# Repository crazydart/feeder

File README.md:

# Feeder REV12CD

Public hardware fork maintained by **crazydart**, derived from [Opulo's feeder repository](https://github.com/opulo-inc/feeder). **REV12CD removes the alternate U2 MCU and keeps U1 (STM32F031C6T6, LQFP-48).** The single board and all three panel copies are labeled REV12CD.

| File | Purpose |
|---|---|
| [Single-board KiCad project](pcb/mobo/mobo.kicad_pro) | Editable circuit and PCB |
| [Three-board KiCad project](pcb/mobo-panel3/feeder-rev12cd-panel3.kicad_pro) | Editable routed panel |
| [JLCPCB upload ZIP](pcb/mobo-panel3/feeder-rev12cd-panel3-jlcpcb.zip) | PCB, drills and both stencil paste layers together |
| [PCB order notes](pcb/mobo-panel3/ORDER-NOTES.md) | Settings and short order comment |
| [Stencil and PnP data](pcb/mobo-panel3/STENCIL-AND-PNP.md) | Stencil settings and saved machine coordinates |
| [Panel documentation](pcb/mobo-panel3/README.md) | Reproduction steps and validation results |

The panel is 184 × 104 × 1.6 mm, with three boards and six drilled breakaway tabs per board. The top/bottom tabs and four side tabs avoid the connectors and buttons.

Modified 2026-10-11 from upstream commit `05843dd0e7551cbf20dc831514174f446f376858`. Checks found no new electrical DRC errors, unconnected items or single-board schematic/PCB mismatches. Inherited DRC/ERC findings are documented in the [single-board notes](pcb/mobo/README.md) and [panel validation reports](pcb/mobo-panel3/validation). This derivative has not been physically prototyped.

Hardware remains under CERN-OHL-W v2; see [LICENSE](LICENSE). The modified PCBs use AI Herding Cats branding and credit Opulo for the original design. Other upstream designs and documentation remain below.

## Accessories

- [Gridfinity holder for 8 mm feeders](cad/accessories/gridfinity-8mm-holder/README.md) — five slots on a 5 × 3 base, with STL and editable OpenSCAD source. Prototype 06 provides 10 mm of feeder lift and 4 mm radial rear relief for mounted reels; revised reel clearance awaits a physical fit check.
- [Gridfinity holder for 16 mm and 24 mm feeders](cad/accessories/gridfinity-2u-holder/README.md) — four slots on a 5 × 4 base, rendered with both 2u feeder models. Physical fit is untested.
- [Continuous 4 mm spool arm and threaded thimble](cad/accessories/threaded-thimble/README.md) — full arm thickness up to the cover-tape guard, with 12.4 mm of reel space and the tested retaining screw with its 30 × 3 mm head. Prototype 04 has no tapered neck; loaded stiffness awaits a print test.

## Parts sourcing

- [Feeder motor sourcing](docs/motor-sourcing.md) — motor specifications, supplier URLs, fit and wiring details, and the October 16, 2026 checkout costs for comparing direct imports with the Opulo kit.

## Upstream LumenPnP Feeders
The LumenPnP Feeders are open source pick and place feeders to aid in [Mid-Scale Manufacturing](https://stephenhawes.com/level-2-manufacturing/).

LumenPnP Feeders are available for sale on the [Opulo Website](https://www.opulo.io/). If you build or buy one, please help the project by documenting bugs with a GitHub issue.

The LumenPnP Feeders run [Photon](https://github.com/photonfirmware/photon), an open source firmware project for pick and place feeders. The popular pick and place control software [OpenPnP](https://openpnp.org/) has Photon support built in, so it's easy to get going with the LumenPnP feeders using your existing OpenPnP setup. These feeders are designed to work with the [LumenPnP](https://opulo.io/products/lumenpnp).

The development process is being cataloged in a series of videos. A playlist of these can be found [here](https://www.youtube.com/playlist?list=PLIeJXmcg1baLBz3x0nCDqkYpKs2IWGHk4).

## Documentation
Feeder user documentation can be found on the [Opulo Docs Page](https://docs.opulo.io/). Open Hardware Assembly instructions can be found at [ohai.opulo.io](https://ohai.opulo.io/).

## Community
Discussion about the project happens on the [STR Discord server](https://discordapp.com/invite/TCwy6De)!

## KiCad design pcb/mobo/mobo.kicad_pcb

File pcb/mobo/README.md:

# Feeder motherboard REV12CD

Open **mobo.kicad_pro** in KiCad 10. The schematic and single-board PCB use **U1, STM32F031C6T6 (LQFP-48)**. U2 and its isolated schematic block are removed, along with 61 PCB track segments that served only its pads. Shared vias and routing needed by U1 are retained.

The remaining component locations, 247 pads, 842 tracks/vias and schematic connections match upstream REV12. R18 and R19 remain 1 MΩ. No firmware or pin assignment changes are introduced. The original board outline and holes remain unchanged.

The silkscreen identifies this derivative as **Feeder REV12CD / AI Herding Cats**. Upstream product branding was removed from the modified board; the open-hardware symbol and upstream copyright/license attribution are retained. Custom footprint paths are relative to this repository. The historical MHS110FRGBCT footprint is included in `../../lib/kicad/index.pretty` so D1 resolves without the upstream author's local library.

The single-board artwork places the **AI Herding Cats** robot-and-cat logo and name on the back silkscreen, oriented for the assembled feeder. **Feeder REV12CD**, **SN:**, **aiherdingcats.com**, and **github.com/crazydart/feeder** appear near the solid white **20 × 6 mm** write-in area, sized for four handwritten serial-number characters. The back explicitly credits **Original design: Opulo / Open-source hardware**. The front branding also reads **AI Herding Cats**. The artwork introduces no new DRC findings; the electrical design is unchanged. Both previews show the installed orientation. [Back preview](back-silkscreen-preview.png) · [Front preview](front-silkscreen-preview.png) · [Original vector logo and placement notes](artwork/README.md).

## Three-board panel and manufacturing

Open [../mobo-panel3/feeder-rev12cd-panel3.kicad_pro](../mobo-panel3/feeder-rev12cd-panel3.kicad_pro) for the editable panel. The panel is generated from this single-board master and contains three electrically separate copies with unique CAD references.

**The panel and fabrication ZIP include the finished artwork on all three copies.** The panel manifest records checksums of this source, the original vector logo, assembly data and manufacturing files.

See the [panel README](../mobo-panel3/README.md), [ordering instructions](../mobo-panel3/ORDER-NOTES.md), and [stencil/PnP handoff](../mobo-panel3/STENCIL-AND-PNP.md). The current [BOM](bom/rev12cd-bom.csv) includes population notes. D1/D3 and the optional programming headers still require a final assembly choice; U2 is absent.

The old upstream STEP and interactive BOM were removed because they represented the previous board. The native KiCad board and current catalog/placement files are authoritative.

## Validation and provenance

KiCad schematic-to-PCB parity: **zero issues**. Board connectivity: **zero unconnected items**. Three inherited thermal-relief findings (U7 pad 4, U8 pad 4 and C3 pad 1) and one inherited TP3/J3 courtyard overlap remain. The schematic retains 17 upstream ERC errors; removing U2 adds three isolated-label warnings for the unused U1 PA0/PA1/PA3 signals. These findings are recorded, not hidden by exclusions. See [validation reports](../mobo-panel3/validation).

Modified 2026-10-11 by crazydart from [opulo-inc/feeder](https://github.com/opulo-inc/feeder), commit `05843dd0e7551cbf20dc831514174f446f376858`. This is an independently modified REV12 board, not an upstream revision or the earlier REV12B experiment. Hardware remains under CERN-OHL-W v2; see [LICENSE](../../LICENSE).

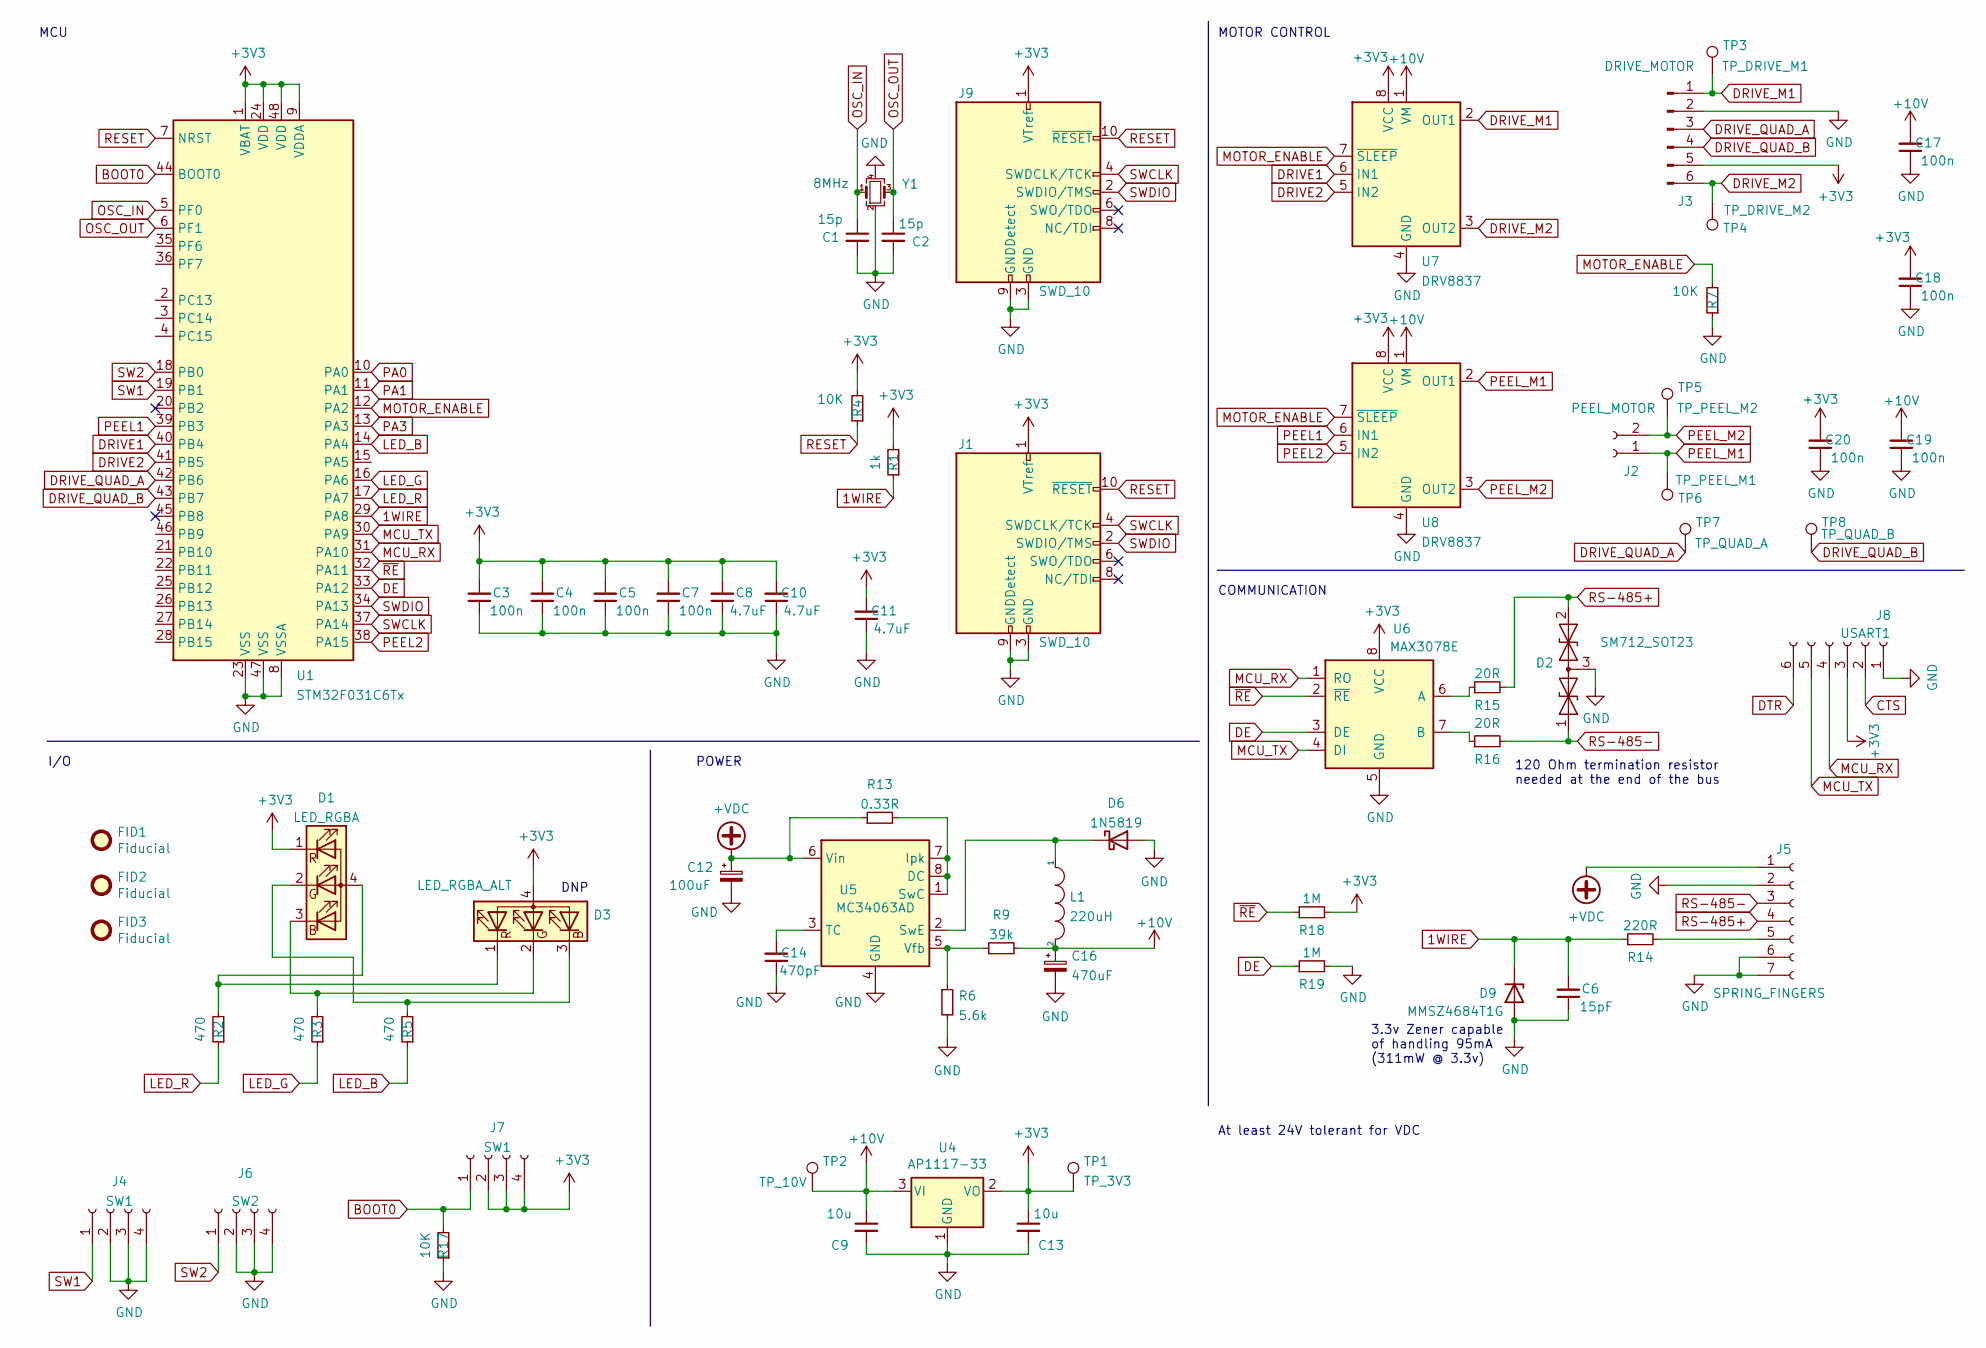
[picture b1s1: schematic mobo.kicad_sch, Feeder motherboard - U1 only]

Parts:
C1, C2: 15p; C_0805_2012Metric; JLCPCB C1794
C3, C4, C5, C7, C17, C18, C19, C20: 100n; C_0805_2012Metric; JLCPCB C49678
C6: 15pF; C_0805_2012Metric; JLCPCB C49678
C8, C10, C11: 4.7uF; C_0805_2012Metric; JLCPCB C49678
C9, C13: 10u; C_0805_2012Metric; JLCPCB C15850
C12: 100uF; C_Elec_6.3x7.7
C14: 470pF; C_0805_2012Metric; JLCPCB C49678
C16: 470uF; C_Elec_6.3x7.7
D1: LED_RGBA; MHS110FRGBCT
D2: SM712_SOT23; SOT-23; LCSC C521963
D3: LED_RGBA_ALT; LED_LiteOn_LTST-C19HE1WT
D6: 1N5819; D_SOD-123
D9: MMSZ4684T1G; D_SOD-123; JLCPCB MMSZ4684T1G
FID1, FID2, FID3: Fiducial; Fiducial_1mm_Mask2mm
J1, J9: SWD_10; PinHeader_2x05_P1.27mm_Vertical_SMD
J2: PEEL_MOTOR; Molex_PicoBlade_53261-0271_1x02-1MP_P1.25mm_Horizontal; LCSC C2845379
J3: DRIVE_MOTOR; Molex_PicoBlade_53261-0671_1x06-1MP_P1.25mm_Horizontal; LCSC C2845383
J4, J7: SW1; 1TS003B-1400-3500A-CT; LCSC C319392
J5: SPRING_FINGERS; AVX-9155-005-541
J6: SW2; 1TS003B-1400-3500A-CT; LCSC C319392
J8: USART1; UART_FRICTION_FIT
L1: 220uH; L_6.3x6.3_H3; LCSC C467145
R1: 1k; R_0805_2012Metric; JLCPCB C17513
R2, R3, R5: 470; R_0805_2012Metric; JLCPCB C17710
R4, R7, R17: 10K; R_0805_2012Metric; JLCPCB C17513
R6: 5.6k; R_0805_2012Metric
R9: 39k; R_0805_2012Metric
R13: 0.33R; R_0805_2012Metric
R14: 220R; R_0805_2012Metric
R15, R16: 20R; R_0805_2012Metric
R18, R19: 1M; R_0805_2012Metric
TP1: TP_3V3; TestPoint_Pad_D2.0mm
TP2: TP_10V; TestPoint_Pad_D2.0mm
TP3: TP_DRIVE_M1; TestPoint_Pad_D2.0mm
TP4: TP_DRIVE_M2; TestPoint_Pad_D2.0mm
TP5: TP_PEEL_M2; TestPoint_Pad_D2.0mm
TP6: TP_PEEL_M1; TestPoint_Pad_D2.0mm
TP7: TP_QUAD_A; TestPoint_Pad_D2.0mm
TP8: TP_QUAD_B; TestPoint_Pad_D2.0mm
U1: STM32F031C6Tx; LQFP-48_7x7mm_P0.5mm
U4: AP1117-33; SOT-223-3_TabPin2; JLCPCB C108785
U5: MC34063AD; SOIC-8_3.9x4.9mm_P1.27mm
U6: MAX3078E; SOIC-8_3.9x4.9mm_P1.27mm; JLCPCB C40031
U7, U8: DRV8837; WSON-8-1EP_2x2mm_P0.5mm_EP0.9x1.6mm
Y1: 8MHz; Crystal_SMD_3225-4Pin_3.2x2.5mm_HandSoldering; JLCPCB C253751

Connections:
1WIRE: C6.2, D9.1 (K), R1.1, R14.1, U1.29 (PA8)
+3V3: C3.2, C4.2, C5.2, C7.2, C8.2, C10.2, C11.2, C13.1, C18.2, C20.2, D1.1 (RK), D3.4 (A), J1.1 (VTref), J3.5, J7.2, J7.3, J7.4, J8.3, J9.1 (VTref), R1.2, R4.2, R18.2, TP1.1, U1.1 (VBAT), U1.9 (VDDA), U1.24 (VDD), U1.48 (VDD), U4.2 (VO), U6.8 (VCC), U7.8 (VCC), U8.8 (VCC)
+10V: C9.1, C16.1, C17.2, C19.2, L1.2, R9.2, TP2.1, U4.3 (VI), U7.1 (VM), U8.1 (VM)
+VDC: C12.1, J5.1, R13.1, U5.6 (Vin)
BOOT0: J7.1, R17.2, U1.44 (BOOT0)
CTS: J8.2
DE: R19.1, U1.33 (PA12), U6.3 (DE)
DRIVE1: U1.40 (PB4), U7.6 (IN1)
DRIVE2: U1.41 (PB5), U7.5 (IN2)
DRIVE_M1: J3.1, TP3.1, U7.2 (OUT1)
DRIVE_M2: J3.6, TP4.1, U7.3 (OUT2)
DRIVE_QUAD_A: J3.3, TP7.1, U1.42 (PB6)
DRIVE_QUAD_B: J3.4, TP8.1, U1.43 (PB7)
DTR: J8.6
GND: C1.2, C2.2, C3.1, C4.1, C5.1, C6.1, C7.1, C8.1, C9.2, C10.1, C11.1, C12.2, C13.2, C14.1, C16.2, C17.1, C18.1, C19.1, C20.1, D2.3 (common), D6.2 (A), D9.2 (A), J1.3 (GND), J1.5 (GND), J1.9 (GNDDetect), J3.2, J4.2, J4.3, J4.4, J5.2, J5.6, J5.7, J6.2, J6.3, J6.4, J8.1, J9.3 (GND), J9.5 (GND), J9.9 (GNDDetect), R6.2, R7.1, R17.1, R19.2, U1.8 (VSSA), U1.23 (VSS), U1.47 (VSS), U4.1 (GND), U5.4 (GND), U6.5 (GND), U7.4 (GND), U7.9 (GND), U8.4 (GND), U8.9 (GND), Y1.2, Y1.4
LED_B: R5.1, U1.14 (PA4)
LED_G: R3.1, U1.16 (PA6)
LED_R: R2.1, U1.17 (PA7)
MCU_RX: J8.4, U1.31 (PA10), U6.1 (RO)
MCU_TX: J8.5, U1.30 (PA9), U6.4 (DI)
MOTOR_ENABLE: R7.2, U1.12 (PA2), U7.7 (~SLEEP), U8.7 (~SLEEP)
unnamed: D1.4 (A), D3.1 (RK), R2.2
unnamed: D1.3 (BK), D3.2 (GK), R3.2
unnamed: D1.2 (GK), D3.3 (BK), R5.2
unnamed: D6.1 (K), L1.1, U5.2 (SwE)
unnamed: J5.5, R14.2
unnamed: R13.2, U5.1 (SwC), U5.7 (Ipk), U5.8 (DC)
unnamed: C14.2, U5.3 (TC)
unnamed: R6.1, R9.1, U5.5 (Vfb)
unnamed: R15.1, U6.6 (A)
unnamed: R16.1, U6.7 (B)
OSC_IN: C1.1, U1.5 (PF0), Y1.1
OSC_OUT: C2.1, U1.6 (PF1), Y1.3
PA0: U1.10 (PA0)
PA1: U1.11 (PA1)
PA3: U1.13 (PA3)
PEEL1: U1.39 (PB3), U8.6 (IN1)
PEEL2: U1.38 (PA15), U8.5 (IN2)
PEEL_M1: J2.1, TP6.1, U8.2 (OUT1)
PEEL_M2: J2.2, TP5.1, U8.3 (OUT2)
RESET: J1.10 (~RESET), J9.10 (~RESET), R4.1, U1.7 (NRST)
RS-485+: D2.2 (A2), J5.4, R15.2
RS-485-: D2.1 (A1), J5.3, R16.2
SW1: J4.1, U1.19 (PB1)
SW2: J6.1, U1.18 (PB0)
SWCLK: J1.4 (SWDCLK/TCK), J9.4 (SWDCLK/TCK), U1.37 (PA14)
SWDIO: J1.2 (SWDIO/TMS), J9.2 (SWDIO/TMS), U1.34 (PA13)
~RE: R18.1, U1.32 (PA11), U6.2 (~RE)

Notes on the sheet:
I/O
DNP
COMMUNICATION
MOTOR CONTROL
POWER
3.3v Zener capable of handling 95mA (311mW @ 3.3v)
At least 24V tolerant for VDC
MCU
120 Ohm termination resistor needed at the end of the bus

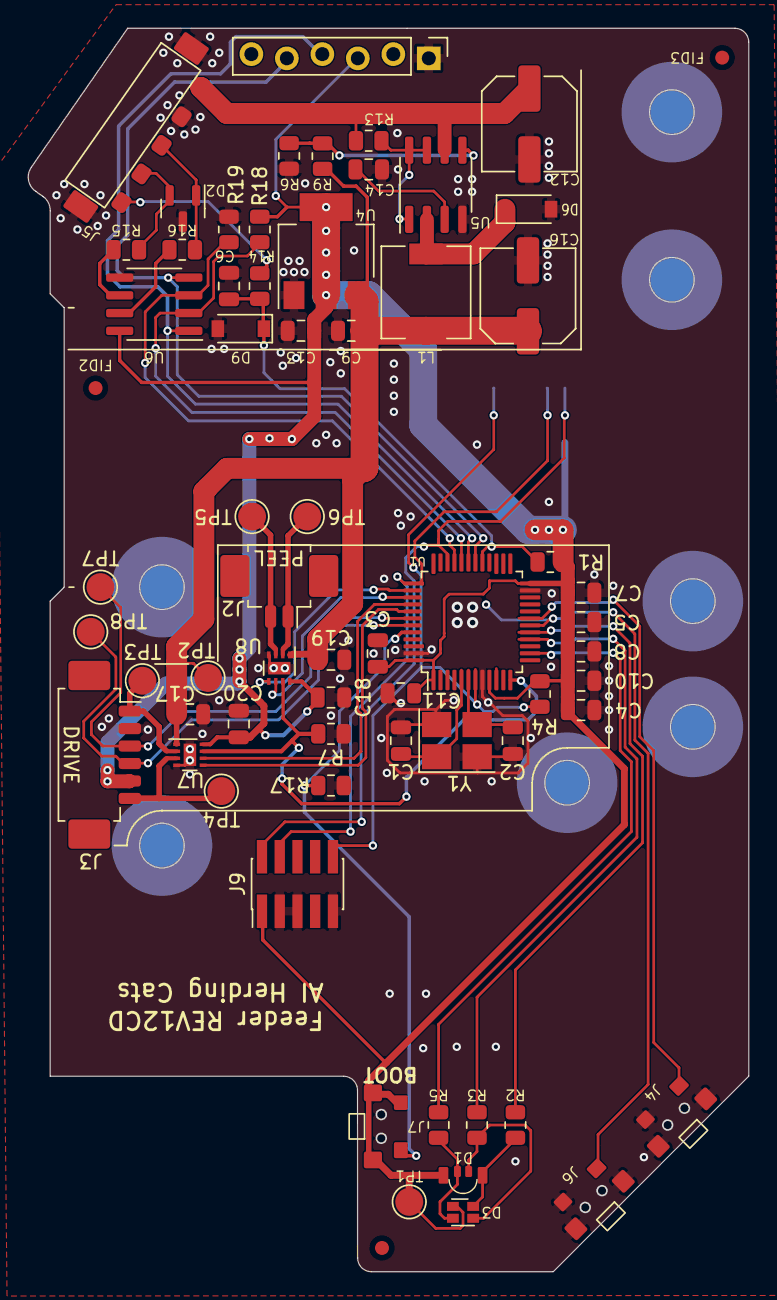
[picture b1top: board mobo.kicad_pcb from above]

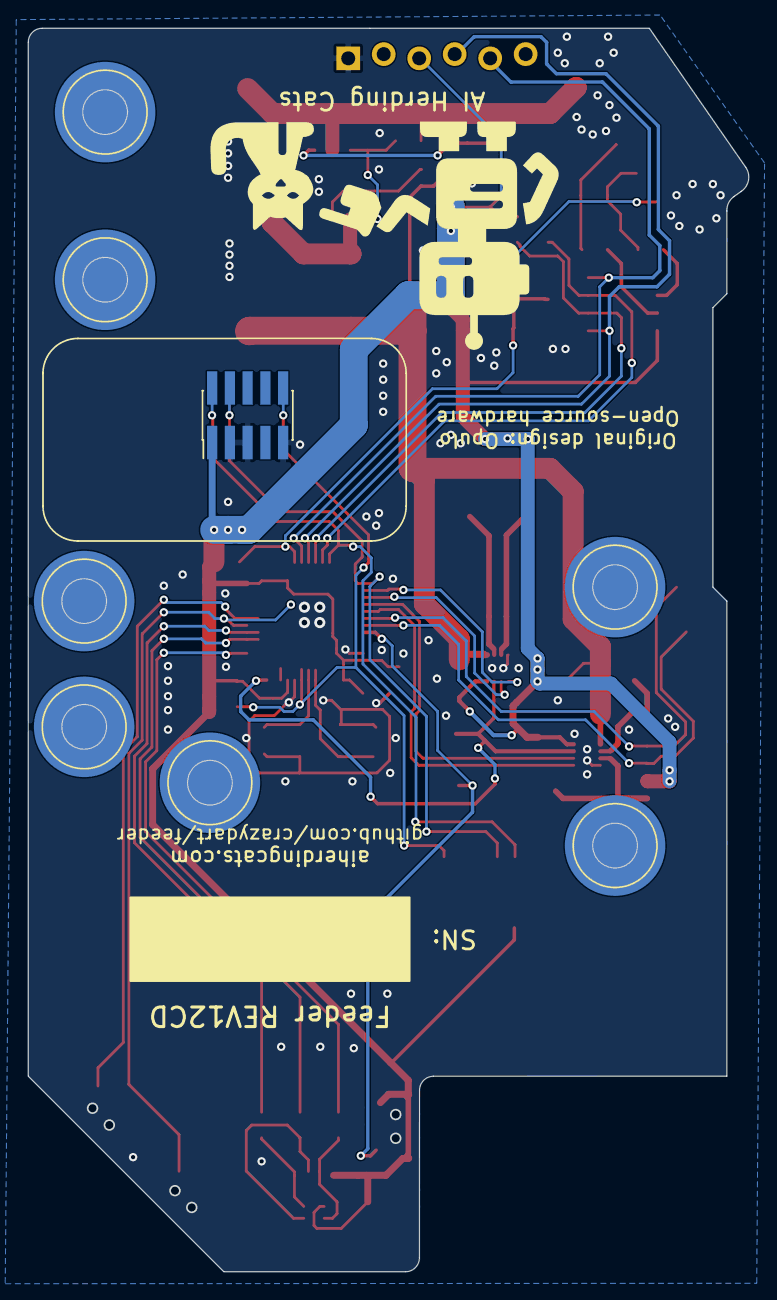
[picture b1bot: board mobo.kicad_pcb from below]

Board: 2 copper layers, 51.6 x 89.0 mm, 68 parts (2 on the bottom side), 43 nets.

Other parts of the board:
GFX1: OSHW-Symbol_6.7x6mm_Mask

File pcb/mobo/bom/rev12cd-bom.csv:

References,Value,Footprint,Quantity per board,Quantity per 3-board panel,Assembly note
R13,0.33R,Resistor_SMD:R_0805_2012Metric,1,3,
"C3, C4, C5, C7, C17, C18, C19, C20",100n,Capacitor_SMD:C_0805_2012Metric,8,24,
C12,100uF,Capacitor_SMD:C_Elec_6.3x7.7,1,3,
"R4, R7, R17",10K,Resistor_SMD:R_0805_2012Metric,3,9,
"C9, C13",10u,Capacitor_SMD:C_0805_2012Metric,2,6,
"C1, C2",15p,Capacitor_SMD:C_0805_2012Metric,2,6,
C6,15pF,Capacitor_SMD:C_0805_2012Metric,1,3,
"R18, R19",1M,Resistor_SMD:R_0805_2012Metric,2,6,
D6,1N5819,Diode_SMD:D_SOD-123,1,3,
R1,1k,Resistor_SMD:R_0805_2012Metric,1,3,
"R15, R16",20R,Resistor_SMD:R_0805_2012Metric,2,6,
R14,220R,Resistor_SMD:R_0805_2012Metric,1,3,
L1,220uH,Inductor_SMD:L_6.3x6.3_H3,1,3,
R9,39k,Resistor_SMD:R_0805_2012Metric,1,3,
"C8, C10, C11",4.7uF,Capacitor_SMD:C_0805_2012Metric,3,9,
"R2, R3, R5",470,Resistor_SMD:R_0805_2012Metric,3,9,
C14,470pF,Capacitor_SMD:C_0805_2012Metric,1,3,
C16,470uF,Capacitor_SMD:C_Elec_6.3x7.7,1,3,
R6,5.6k,Resistor_SMD:R_0805_2012Metric,1,3,
Y1,8MHz,Crystal:Crystal_SMD_3225-4Pin_3.2x2.5mm_HandSoldering,1,3,
U4,AP1117-33,Package_TO_SOT_SMD:SOT-223-3_TabPin2,1,3,
J3,DRIVE_MOTOR,Connector_Molex:Molex_PicoBlade_53261-0671_1x06-1MP_P1.25mm_Horizontal,1,3,
"U7, U8",DRV8837,Package_SON:WSON-8-1EP_2x2mm_P0.5mm_EP0.9x1.6mm,2,6,
D1,LED_RGBA,index:MHS110FRGBCT,1,3,Choose D1 or D3 LED option before programming
D3,LED_RGBA_ALT,LED_SMD:LED_LiteOn_LTST-C19HE1WT,1,3,Choose D1 or D3 LED option before programming
U6,MAX3078E,Package_SO:SOIC-8_3.9x4.9mm_P1.27mm,1,3,
U5,MC34063AD,Package_SO:SOIC-8_3.9x4.9mm_P1.27mm,1,3,
D9,MMSZ4684T1G,Diode_SMD:D_SOD-123,1,3,
J2,PEEL_MOTOR,Connector_Molex:Molex_PicoBlade_53261-0271_1x02-1MP_P1.25mm_Horizontal,1,3,
D2,SM712_SOT23,Package_TO_SOT_SMD:SOT-23,1,3,
J5,SPRING_FINGERS,feeder:AVX-9155-005-541,1,3,
U1,STM32F031C6Tx,Package_QFP:LQFP-48_7x7mm_P0.5mm,1,3,
"J4, J7",SW1,feeder:1TS003B-1400-3500A-CT,2,6,
J6,SW2,feeder:1TS003B-1400-3500A-CT,1,3,
"J1, J9",SWD_10,Connector_PinHeader_1.27mm:PinHeader_2x05_P1.27mm_Vertical_SMD,2,6,Optional SWD programming header; confirm population
J8,USART1,feeder:UART_FRICTION_FIT,1,3,

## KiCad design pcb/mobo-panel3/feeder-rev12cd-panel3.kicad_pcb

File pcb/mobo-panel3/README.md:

# REV12CD — three-board routed panel

Open **[feeder-rev12cd-panel3.kicad_pro](feeder-rev12cd-panel3.kicad_pro)** in KiCad 10, then open its PCB. This is a real editable KiCad panel with three copies of the [single-board REV12CD source](../mobo/mobo.kicad_pro). U2 is removed from every copy. Each board's silkscreen reads **REV12CD**.

All three copies include the AI Herding Cats vector logo, website, repository URL, 20 × 6 mm serial-number box and **Original design: Opulo / Open-source hardware** credit. Back artwork reads upright in the installed feeder. Each logo and caption remains an editable KiCad group. [Panel front](top-gerber-preview.png).

The panel is **184 × 104 × 1.6 mm**, three columns at **59 mm pitch**, with six drilled tabs per board. The four side tabs and requested top/bottom tabs are retained. It uses 18 tabs, 144 × 0.6 mm NPTH holes at 1 mm pitch, and 2 mm routed channels. There are no V-cuts. [Annotated tab placement](tab-placement-preview.png).

## Files to use

- **[feeder-rev12cd-panel3-jlcpcb.zip](feeder-rev12cd-panel3-jlcpcb.zip):** the PCB upload, including both paste layers in the same ZIP. Nine Gerbers and two Excellon files.
- **[ORDER-NOTES.md](ORDER-NOTES.md):** fabrication settings, counts and short PCB order comment.
- **[STENCIL-AND-PNP.md](STENCIL-AND-PNP.md):** 0.10 mm top-stencil recommendation and machine setup data.
- **[assembly/](assembly):** full component catalog, 165 candidate SMD placements, fiducials, panel offsets and stencil settings.
- **[validation/](validation):** PCB/schematic comparison, DRC/ERC, routing, drill, paste and placement checks.
- **[MANIFEST.json](MANIFEST.json):** checksums for fabrication, source, assembly and validation files.

The panel has its own PCB project for layout and manufacturing. Edit the circuit in the single-board schematic; regenerate the panel afterward. Do not update the three-copy panel directly from the single-board schematic.

## Reproduction

Dependencies: KiCad **10.0.3**, its bundled Python (`pcbnew` and `wx`), and Python 3.11 with **Shapely 2.0.7**, Gerbonara, CairoSVG, Pillow and NumPy. The scripts use `kicad-cli` on PATH, with a macOS application fallback. The preview renderer uses Cairo; on macOS its library path may need to include KiCad's Frameworks directory.

From the repository root:

1. Edit `pcb/mobo/mobo.kicad_sch` / `.kicad_pcb`. Refill the unit with `kicad-cli pcb drc --refill-zones --save-board --schematic-parity --format json --output pcb/mobo-panel3/validation/unit-drc.json pcb/mobo/mobo.kicad_pcb`.
2. Run `pcb/mobo-panel3/tools/export_component_bounds.py` with KiCad's Python, then `build_panel.py` with the geometry Python environment.
3. Refill the panel with `kicad-cli pcb drc --refill-zones --save-board --format json --output pcb/mobo-panel3/validation/drc.json pcb/mobo-panel3/feeder-rev12cd-panel3.kicad_pcb`.
4. Run `export_fabrication.py` using standard Python. It includes the paste and PnP export.
5. Run `validate_unit.py` with standard Python and `verify_panel.py` with KiCad's Python. The former requires the recorded upstream commit in Git history.
6. Run `validate_fabrication.py` and `validate_stencil.py` with the geometry/Gerber dependencies. Run `kicad-cli sch erc --format json --output pcb/mobo-panel3/validation/unit-erc.json pcb/mobo/mobo.kicad_sch` for the schematic report.
7. Run `render_gerbers.py pcb/mobo-panel3`, then `render_tab_preview.py`.
8. Run `package_order.py` to rebuild the upload ZIP, BOM and checksums. Inspect changes before publishing a new revision.

The scripts assert expected board counts, footprint/pad correspondence, clearance and the known inherited DRC findings. An assertion failure requires investigation; it should not be bypassed to generate an order.

## Validation result

The panel has 204 non-tab footprints, 741 original pads and 2,526 tracks/vias matching three translated unit boards. Silkscreen checks verify all copied text, all 21 logo polygons, three serial-number boxes and three editable logo groups against the single board. The 144 additional pads are exclusively NPTH breakaway holes. Minimum tab-to-connector/button footprint clearance is **3.15 mm**; a raster check of exported copper gives a conservative **0.69 mm** minimum clearance from the tab-hole rims. Separating all perforation rows yields exactly three boards and the frame.

No shorts, electrical clearance errors, dangling tracks or unconnected items were found. The panel retains nine source thermal-relief findings, three TP3/J3 courtyard overlaps and 264 library/silkscreen warnings. The separate unit schematic retains upstream ERC findings documented in [../mobo/README.md](../mobo/README.md). This panel has not been physically prototyped.

Artwork panel regenerated 2026-10-12 from single-board commit `5a49448`. Modified by crazydart; derived from Opulo REV12. Hardware attribution and CERN-OHL-W v2 licensing remain in [LICENSE](../../LICENSE). The modified boards use AI Herding Cats branding and credit the original Opulo design.

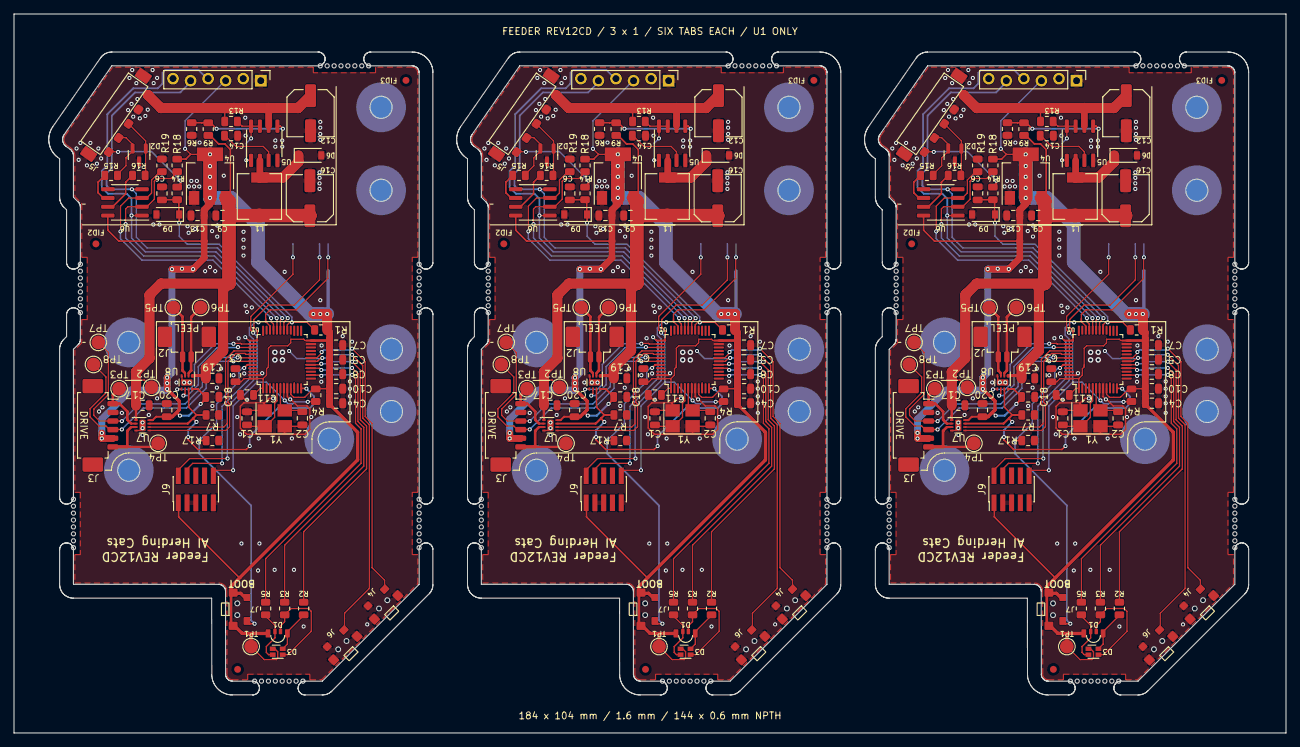
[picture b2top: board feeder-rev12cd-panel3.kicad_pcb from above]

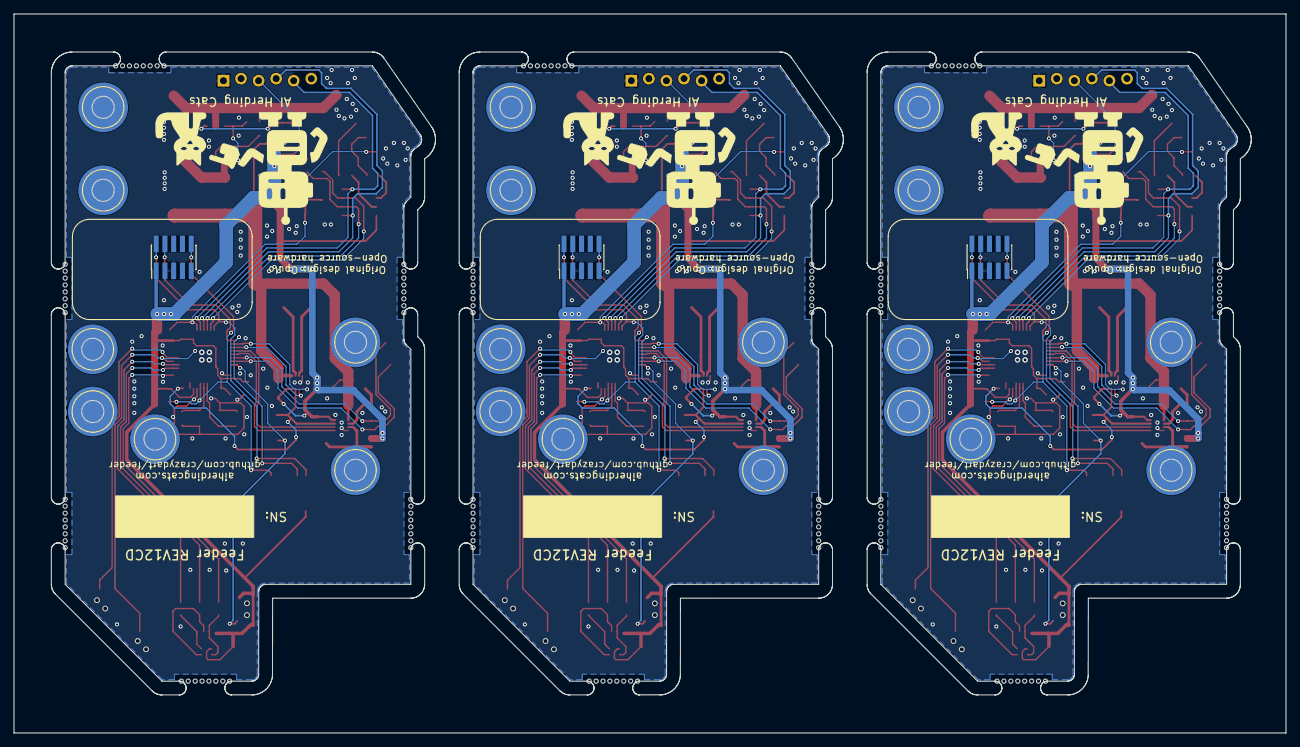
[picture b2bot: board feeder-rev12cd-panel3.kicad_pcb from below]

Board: 2 copper layers, 184.0 x 104.0 mm, 205 parts (6 on the bottom side), 129 nets.

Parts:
MB1: 144 x 0.6 mm NPTH; PanelMouseBites
P1_C1, P1_C2, P2_C1, P2_C2, P3_C1, P3_C2: 15p; C_0805_2012Metric
P1_C3, P1_C4, P1_C5, P1_C7, P1_C17, P1_C18, P1_C19, P1_C20, P2_C3, P2_C4, P2_C5, P2_C7, P2_C17, P2_C18, P2_C19, P2_C20, P3_C3, P3_C4, P3_C5, P3_C7, P3_C17, P3_C18, P3_C19, P3_C20: 100n; C_0805_2012Metric
P1_C6, P2_C6, P3_C6: 15pF; C_0805_2012Metric
P1_C8, P1_C10, P1_C11, P2_C8, P2_C10, P2_C11, P3_C8, P3_C10, P3_C11: 4.7uF; C_0805_2012Metric
P1_C9, P1_C13, P2_C9, P2_C13, P3_C9, P3_C13: 10u; C_0805_2012Metric
P1_C12, P2_C12, P3_C12: 100uF; C_Elec_6.3x7.7
P1_C14, P2_C14, P3_C14: 470pF; C_0805_2012Metric
P1_C16, P2_C16, P3_C16: 470uF; C_Elec_6.3x7.7
P1_D1, P2_D1, P3_D1: LED_RGBA; MHS110FRGBCT
P1_D2, P2_D2, P3_D2: SM712_SOT23; SOT-23
P1_D3, P2_D3, P3_D3: LED_RGBA_ALT; LED_LiteOn_LTST-C19HE1WT
P1_D6, P2_D6, P3_D6: 1N5819; D_SOD-123
P1_D9, P2_D9, P3_D9: MMSZ4684T1G; D_SOD-123
P1_FID1, P1_FID2, P1_FID3, P2_FID1, P2_FID2, P2_FID3, P3_FID1, P3_FID2, P3_FID3: Fiducial; Fiducial_1mm_Mask2mm
P1_GFX1, P2_GFX1, P3_GFX1: OSHW-Symbol_6.7x6mm_Mask
P1_J1, P1_J9, P2_J1, P2_J9, P3_J1, P3_J9: SWD_10; PinHeader_2x05_P1.27mm_Vertical_SMD
P1_J2, P2_J2, P3_J2: PEEL_MOTOR; Molex_PicoBlade_53261-0271_1x02-1MP_P1.25mm_Horizontal
P1_J3, P2_J3, P3_J3: DRIVE_MOTOR; Molex_PicoBlade_53261-0671_1x06-1MP_P1.25mm_Horizontal
P1_J4, P1_J7, P2_J4, P2_J7, P3_J4, P3_J7: SW1; 1TS003B-1400-3500A-CT
P1_J5, P2_J5, P3_J5: SPRING_FINGERS; AVX-9155-005-541
P1_J6, P2_J6, P3_J6: SW2; 1TS003B-1400-3500A-CT
P1_J8, P2_J8, P3_J8: USART1; UART_FRICTION_FIT
P1_L1, P2_L1, P3_L1: 220uH; L_6.3x6.3_H3
P1_R1, P2_R1, P3_R1: 1k; R_0805_2012Metric
P1_R2, P1_R3, P1_R5, P2_R2, P2_R3, P2_R5, P3_R2, P3_R3, P3_R5: 470; R_0805_2012Metric
P1_R4, P1_R7, P1_R17, P2_R4, P2_R7, P2_R17, P3_R4, P3_R7, P3_R17: 10K; R_0805_2012Metric
P1_R6, P2_R6, P3_R6: 5.6k; R_0805_2012Metric
P1_R9, P2_R9, P3_R9: 39k; R_0805_2012Metric
P1_R13, P2_R13, P3_R13: 0.33R; R_0805_2012Metric
P1_R14, P2_R14, P3_R14: 220R; R_0805_2012Metric
P1_R15, P1_R16, P2_R15, P2_R16, P3_R15, P3_R16: 20R; R_0805_2012Metric
P1_R18, P1_R19, P2_R18, P2_R19, P3_R18, P3_R19: 1M; R_0805_2012Metric
P1_TP1, P2_TP1, P3_TP1: TP_3V3; TestPoint_Pad_D2.0mm
P1_TP2, P2_TP2, P3_TP2: TP_10V; TestPoint_Pad_D2.0mm
P1_TP3, P2_TP3, P3_TP3: TP_DRIVE_M1; TestPoint_Pad_D2.0mm
P1_TP4, P2_TP4, P3_TP4: TP_DRIVE_M2; TestPoint_Pad_D2.0mm
P1_TP5, P2_TP5, P3_TP5: TP_PEEL_M2; TestPoint_Pad_D2.0mm
P1_TP6, P2_TP6, P3_TP6: TP_PEEL_M1; TestPoint_Pad_D2.0mm
P1_TP7, P2_TP7, P3_TP7: TP_QUAD_A; TestPoint_Pad_D2.0mm
P1_TP8, P2_TP8, P3_TP8: TP_QUAD_B; TestPoint_Pad_D2.0mm
P1_U1, P2_U1, P3_U1: STM32F031C6Tx; LQFP-48_7x7mm_P0.5mm
P1_U4, P2_U4, P3_U4: AP1117-33; SOT-223-3_TabPin2
P1_U5, P2_U5, P3_U5: MC34063AD; SOIC-8_3.9x4.9mm_P1.27mm
P1_U6, P2_U6, P3_U6: MAX3078E; SOIC-8_3.9x4.9mm_P1.27mm
P1_U7, P1_U8, P2_U7, P2_U8, P3_U7, P3_U8: DRV8837; WSON-8-1EP_2x2mm_P0.5mm_EP0.9x1.6mm
P1_Y1, P2_Y1, P3_Y1: 8MHz; Crystal_SMD_3225-4Pin_3.2x2.5mm_HandSoldering

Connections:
P1/1WIRE: P1_C6.2, P1_D9.1 (K), P1_R1.1, P1_R14.1, P1_U1.29 (PA8)
P1/+3V3: P1_C3.2, P1_C4.2, P1_C5.2, P1_C7.2, P1_C8.2, P1_C10.2, P1_C11.2, P1_C13.1, P1_C18.2, P1_C20.2, P1_D1.1 (RK), P1_D3.4 (A), P1_J1.1 (VTref), P1_J3.5, P1_J7.2, P1_J7.3, P1_J7.4, P1_J8.3, P1_J9.1 (VTref), P1_R1.2, P1_R4.2, P1_R18.2, P1_TP1.1, P1_U1.1 (VBAT), P1_U1.9 (VDDA), P1_U1.24 (VDD), P1_U1.48 (VDD), P1_U4.2 (VO), P1_U6.8 (VCC), P1_U7.8 (VCC), P1_U8.8 (VCC)
P1/+10V: P1_C9.1, P1_C16.1, P1_C17.2, P1_C19.2, P1_L1.2, P1_R9.2, P1_TP2.1, P1_U4.3 (VI), P1_U7.1 (VM), P1_U8.1 (VM)
P1/+VDC: P1_C12.1, P1_J5.1, P1_R13.1, P1_U5.6 (Vin)
P1/BOOT0: P1_J7.1, P1_R17.2, P1_U1.44 (BOOT0)
P1/DE: P1_R19.1, P1_U1.33 (PA12), P1_U6.3 (DE)
P1/DRIVE1: P1_U1.40 (PB4), P1_U7.6 (IN1)
P1/DRIVE2: P1_U1.41 (PB5), P1_U7.5 (IN2)
P1/DRIVE_M1: P1_J3.1, P1_TP3.1, P1_U7.2 (OUT1)
P1/DRIVE_M2: P1_J3.6, P1_TP4.1, P1_U7.3 (OUT2)
P1/DRIVE_QUAD_A: P1_J3.3, P1_TP7.1, P1_U1.42 (PB6)
P1/DRIVE_QUAD_B: P1_J3.4, P1_TP8.1, P1_U1.43 (PB7)
P1/GND: P1_C1.2, P1_C2.2, P1_C3.1, P1_C4.1, P1_C5.1, P1_C6.1, P1_C7.1, P1_C8.1, P1_C9.2, P1_C10.1, P1_C11.1, P1_C12.2, P1_C13.2, P1_C14.1, P1_C16.2, P1_C17.1, P1_C18.1, P1_C19.1, P1_C20.1, P1_D2.3 (common), P1_D6.2 (A), P1_D9.2 (A), P1_J1.3 (GND), P1_J1.5 (GND), P1_J1.9 (GNDDetect), P1_J3.2, P1_J4.2, P1_J4.3, P1_J4.4, P1_J5.2, P1_J5.6, P1_J5.7, P1_J6.2, P1_J6.3, P1_J6.4, P1_J8.1, P1_J9.3 (GND), P1_J9.5 (GND), P1_J9.9 (GNDDetect), P1_R6.2, P1_R7.1, P1_R17.1, P1_R19.2, P1_U1.8 (VSSA), P1_U1.23 (VSS), P1_U1.47 (VSS), P1_U4.1 (GND), P1_U5.4 (GND), P1_U6.5 (GND), P1_U7.4 (GND), P1_U7.9 (GND), P1_U8.4 (GND), P1_U8.9 (GND), P1_Y1.2, P1_Y1.4
P1/LED_B: P1_R5.1, P1_U1.14 (PA4)
P1/LED_G: P1_R3.1, P1_U1.16 (PA6)
P1/LED_R: P1_R2.1, P1_U1.17 (PA7)
P1/MCU_RX: P1_J8.4, P1_U1.31 (PA10), P1_U6.1 (RO)
P1/MCU_TX: P1_J8.5, P1_U1.30 (PA9), P1_U6.4 (DI)
P1/MOTOR_ENABLE: P1_R7.2, P1_U1.12 (PA2), P1_U7.7 (~SLEEP), P1_U8.7 (~SLEEP)
P1/Net-(D1-A): P1_D1.4 (A), P1_D3.1 (RK), P1_R2.2
P1/Net-(D1-BK): P1_D1.3 (BK), P1_D3.2 (GK), P1_R3.2
P1/Net-(D1-GK): P1_D1.2 (GK), P1_D3.3 (BK), P1_R5.2
P1/Net-(D6-K): P1_D6.1 (K), P1_L1.1, P1_U5.2 (SwE)
P1/Net-(J5-Pin_5): P1_J5.5, P1_R14.2
P1/Net-(U5-DC): P1_R13.2, P1_U5.1 (SwC), P1_U5.7 (Ipk), P1_U5.8 (DC)
P1/Net-(U5-TC): P1_C14.2, P1_U5.3 (TC)
P1/Net-(U5-Vfb): P1_R6.1, P1_R9.1, P1_U5.5 (Vfb)
P1/Net-(U6-A): P1_R15.1, P1_U6.6 (A)
P1/Net-(U6-B): P1_R16.1, P1_U6.7 (B)
P1/OSC_IN: P1_C1.1, P1_U1.5 (PF0), P1_Y1.1
P1/OSC_OUT: P1_C2.1, P1_U1.6 (PF1), P1_Y1.3
P1/PEEL1: P1_U1.39 (PB3), P1_U8.6 (IN1)
P1/PEEL2: P1_U1.38 (PA15), P1_U8.5 (IN2)
P1/PEEL_M1: P1_J2.1, P1_TP6.1, P1_U8.2 (OUT1)
P1/PEEL_M2: P1_J2.2, P1_TP5.1, P1_U8.3 (OUT2)
P1/RESET: P1_J1.10 (~RESET), P1_J9.10 (~RESET), P1_R4.1, P1_U1.7 (NRST)
P1/RS-485+: P1_D2.2 (A2), P1_J5.4, P1_R15.2
P1/RS-485-: P1_D2.1 (A1), P1_J5.3, P1_R16.2
P1/SW1: P1_J4.1, P1_U1.19 (PB1)
P1/SW2: P1_J6.1, P1_U1.18 (PB0)
P1/SWCLK: P1_J1.4 (SWDCLK/TCK), P1_J9.4 (SWDCLK/TCK), P1_U1.37 (PA14)
P1/SWDIO: P1_J1.2 (SWDIO/TMS), P1_J9.2 (SWDIO/TMS), P1_U1.34 (PA13)
P1/~RE: P1_R18.1, P1_U1.32 (PA11), P1_U6.2 (~RE)
P2/1WIRE: P2_C6.2, P2_D9.1 (K), P2_R1.1, P2_R14.1, P2_U1.29 (PA8)
P2/+3V3: P2_C3.2, P2_C4.2, P2_C5.2, P2_C7.2, P2_C8.2, P2_C10.2, P2_C11.2, P2_C13.1, P2_C18.2, P2_C20.2, P2_D1.1 (RK), P2_D3.4 (A), P2_J1.1 (VTref), P2_J3.5, P2_J7.2, P2_J7.3, P2_J7.4, P2_J8.3, P2_J9.1 (VTref), P2_R1.2, P2_R4.2, P2_R18.2, P2_TP1.1, P2_U1.1 (VBAT), P2_U1.9 (VDDA), P2_U1.24 (VDD), P2_U1.48 (VDD), P2_U4.2 (VO), P2_U6.8 (VCC), P2_U7.8 (VCC), P2_U8.8 (VCC)
P2/+10V: P2_C9.1, P2_C16.1, P2_C17.2, P2_C19.2, P2_L1.2, P2_R9.2, P2_TP2.1, P2_U4.3 (VI), P2_U7.1 (VM), P2_U8.1 (VM)
P2/+VDC: P2_C12.1, P2_J5.1, P2_R13.1, P2_U5.6 (Vin)
P2/BOOT0: P2_J7.1, P2_R17.2, P2_U1.44 (BOOT0)
P2/DE: P2_R19.1, P2_U1.33 (PA12), P2_U6.3 (DE)
P2/DRIVE1: P2_U1.40 (PB4), P2_U7.6 (IN1)
P2/DRIVE2: P2_U1.41 (PB5), P2_U7.5 (IN2)
P2/DRIVE_M1: P2_J3.1, P2_TP3.1, P2_U7.2 (OUT1)
P2/DRIVE_M2: P2_J3.6, P2_TP4.1, P2_U7.3 (OUT2)
P2/DRIVE_QUAD_A: P2_J3.3, P2_TP7.1, P2_U1.42 (PB6)
P2/DRIVE_QUAD_B: P2_J3.4, P2_TP8.1, P2_U1.43 (PB7)
P2/GND: P2_C1.2, P2_C2.2, P2_C3.1, P2_C4.1, P2_C5.1, P2_C6.1, P2_C7.1, P2_C8.1, P2_C9.2, P2_C10.1, P2_C11.1, P2_C12.2, P2_C13.2, P2_C14.1, P2_C16.2, P2_C17.1, P2_C18.1, P2_C19.1, P2_C20.1, P2_D2.3 (common), P2_D6.2 (A), P2_D9.2 (A), P2_J1.3 (GND), P2_J1.5 (GND), P2_J1.9 (GNDDetect), P2_J3.2, P2_J4.2, P2_J4.3, P2_J4.4, P2_J5.2, P2_J5.6, P2_J5.7, P2_J6.2, P2_J6.3, P2_J6.4, P2_J8.1, P2_J9.3 (GND), P2_J9.5 (GND), P2_J9.9 (GNDDetect), P2_R6.2, P2_R7.1, P2_R17.1, P2_R19.2, P2_U1.8 (VSSA), P2_U1.23 (VSS), P2_U1.47 (VSS), P2_U4.1 (GND), P2_U5.4 (GND), P2_U6.5 (GND), P2_U7.4 (GND), P2_U7.9 (GND), P2_U8.4 (GND), P2_U8.9 (GND), P2_Y1.2, P2_Y1.4
P2/LED_B: P2_R5.1, P2_U1.14 (PA4)
P2/LED_G: P2_R3.1, P2_U1.16 (PA6)
P2/LED_R: P2_R2.1, P2_U1.17 (PA7)
P2/MCU_RX: P2_J8.4, P2_U1.31 (PA10), P2_U6.1 (RO)
P2/MCU_TX: P2_J8.5, P2_U1.30 (PA9), P2_U6.4 (DI)
P2/MOTOR_ENABLE: P2_R7.2, P2_U1.12 (PA2), P2_U7.7 (~SLEEP), P2_U8.7 (~SLEEP)
P2/Net-(D1-A): P2_D1.4 (A), P2_D3.1 (RK), P2_R2.2
P2/Net-(D1-BK): P2_D1.3 (BK), P2_D3.2 (GK), P2_R3.2
P2/Net-(D1-GK): P2_D1.2 (GK), P2_D3.3 (BK), P2_R5.2
P2/Net-(D6-K): P2_D6.1 (K), P2_L1.1, P2_U5.2 (SwE)
P2/Net-(J5-Pin_5): P2_J5.5, P2_R14.2
P2/Net-(U5-DC): P2_R13.2, P2_U5.1 (SwC), P2_U5.7 (Ipk), P2_U5.8 (DC)
P2/Net-(U5-TC): P2_C14.2, P2_U5.3 (TC)
P2/Net-(U5-Vfb): P2_R6.1, P2_R9.1, P2_U5.5 (Vfb)
P2/Net-(U6-A): P2_R15.1, P2_U6.6 (A)
P2/Net-(U6-B): P2_R16.1, P2_U6.7 (B)
P2/OSC_IN: P2_C1.1, P2_U1.5 (PF0), P2_Y1.1
P2/OSC_OUT: P2_C2.1, P2_U1.6 (PF1), P2_Y1.3
P2/PEEL1: P2_U1.39 (PB3), P2_U8.6 (IN1)
P2/PEEL2: P2_U1.38 (PA15), P2_U8.5 (IN2)
P2/PEEL_M1: P2_J2.1, P2_TP6.1, P2_U8.2 (OUT1)
P2/PEEL_M2: P2_J2.2, P2_TP5.1, P2_U8.3 (OUT2)
P2/RESET: P2_J1.10 (~RESET), P2_J9.10 (~RESET), P2_R4.1, P2_U1.7 (NRST)
P2/RS-485+: P2_D2.2 (A2), P2_J5.4, P2_R15.2
P2/RS-485-: P2_D2.1 (A1), P2_J5.3, P2_R16.2
P2/SW1: P2_J4.1, P2_U1.19 (PB1)
P2/SW2: P2_J6.1, P2_U1.18 (PB0)
P2/SWCLK: P2_J1.4 (SWDCLK/TCK), P2_J9.4 (SWDCLK/TCK), P2_U1.37 (PA14)
P2/SWDIO: P2_J1.2 (SWDIO/TMS), P2_J9.2 (SWDIO/TMS), P2_U1.34 (PA13)
P2/~RE: P2_R18.1, P2_U1.32 (PA11), P2_U6.2 (~RE)
P3/1WIRE: P3_C6.2, P3_D9.1 (K), P3_R1.1, P3_R14.1, P3_U1.29 (PA8)
P3/+3V3: P3_C3.2, P3_C4.2, P3_C5.2, P3_C7.2, P3_C8.2, P3_C10.2, P3_C11.2, P3_C13.1, P3_C18.2, P3_C20.2, P3_D1.1 (RK), P3_D3.4 (A), P3_J1.1 (VTref), P3_J3.5, P3_J7.2, P3_J7.3, P3_J7.4, P3_J8.3, P3_J9.1 (VTref), P3_R1.2, P3_R4.2, P3_R18.2, P3_TP1.1, P3_U1.1 (VBAT), P3_U1.9 (VDDA), P3_U1.24 (VDD), P3_U1.48 (VDD), P3_U4.2 (VO), P3_U6.8 (VCC), P3_U7.8 (VCC), P3_U8.8 (VCC)
P3/+10V: P3_C9.1, P3_C16.1, P3_C17.2, P3_C19.2, P3_L1.2, P3_R9.2, P3_TP2.1, P3_U4.3 (VI), P3_U7.1 (VM), P3_U8.1 (VM)
P3/+VDC: P3_C12.1, P3_J5.1, P3_R13.1, P3_U5.6 (Vin)
P3/BOOT0: P3_J7.1, P3_R17.2, P3_U1.44 (BOOT0)
P3/DE: P3_R19.1, P3_U1.33 (PA12), P3_U6.3 (DE)
P3/DRIVE1: P3_U1.40 (PB4), P3_U7.6 (IN1)
P3/DRIVE2: P3_U1.41 (PB5), P3_U7.5 (IN2)
P3/DRIVE_M1: P3_J3.1, P3_TP3.1, P3_U7.2 (OUT1)
P3/DRIVE_M2: P3_J3.6, P3_TP4.1, P3_U7.3 (OUT2)
P3/DRIVE_QUAD_A: P3_J3.3, P3_TP7.1, P3_U1.42 (PB6)
P3/DRIVE_QUAD_B: P3_J3.4, P3_TP8.1, P3_U1.43 (PB7)
P3/GND: P3_C1.2, P3_C2.2, P3_C3.1, P3_C4.1, P3_C5.1, P3_C6.1, P3_C7.1, P3_C8.1, P3_C9.2, P3_C10.1, P3_C11.1, P3_C12.2, P3_C13.2, P3_C14.1, P3_C16.2, P3_C17.1, P3_C18.1, P3_C19.1, P3_C20.1, P3_D2.3 (common), P3_D6.2 (A), P3_D9.2 (A), P3_J1.3 (GND), P3_J1.5 (GND), P3_J1.9 (GNDDetect), P3_J3.2, P3_J4.2, P3_J4.3, P3_J4.4, P3_J5.2, P3_J5.6, P3_J5.7, P3_J6.2, P3_J6.3, P3_J6.4, P3_J8.1, P3_J9.3 (GND), P3_J9.5 (GND), P3_J9.9 (GNDDetect), P3_R6.2, P3_R7.1, P3_R17.1, P3_R19.2, P3_U1.8 (VSSA), P3_U1.23 (VSS), P3_U1.47 (VSS), P3_U4.1 (GND), P3_U5.4 (GND), P3_U6.5 (GND), P3_U7.4 (GND), P3_U7.9 (GND), P3_U8.4 (GND), P3_U8.9 (GND), P3_Y1.2, P3_Y1.4
P3/LED_B: P3_R5.1, P3_U1.14 (PA4)
P3/LED_G: P3_R3.1, P3_U1.16 (PA6)
P3/LED_R: P3_R2.1, P3_U1.17 (PA7)
P3/MCU_RX: P3_J8.4, P3_U1.31 (PA10), P3_U6.1 (RO)
P3/MCU_TX: P3_J8.5, P3_U1.30 (PA9), P3_U6.4 (DI)
P3/MOTOR_ENABLE: P3_R7.2, P3_U1.12 (PA2), P3_U7.7 (~SLEEP), P3_U8.7 (~SLEEP)
P3/Net-(D1-A): P3_D1.4 (A), P3_D3.1 (RK), P3_R2.2
P3/Net-(D1-BK): P3_D1.3 (BK), P3_D3.2 (GK), P3_R3.2
P3/Net-(D1-GK): P3_D1.2 (GK), P3_D3.3 (BK), P3_R5.2
P3/Net-(D6-K): P3_D6.1 (K), P3_L1.1, P3_U5.2 (SwE)
P3/Net-(J5-Pin_5): P3_J5.5, P3_R14.2
P3/Net-(U5-DC): P3_R13.2, P3_U5.1 (SwC), P3_U5.7 (Ipk), P3_U5.8 (DC)
P3/Net-(U5-TC): P3_C14.2, P3_U5.3 (TC)
P3/Net-(U5-Vfb): P3_R6.1, P3_R9.1, P3_U5.5 (Vfb)
P3/Net-(U6-A): P3_R15.1, P3_U6.6 (A)
P3/Net-(U6-B): P3_R16.1, P3_U6.7 (B)
P3/OSC_IN: P3_C1.1, P3_U1.5 (PF0), P3_Y1.1
P3/OSC_OUT: P3_C2.1, P3_U1.6 (PF1), P3_Y1.3
P3/PEEL1: P3_U1.39 (PB3), P3_U8.6 (IN1)
P3/PEEL2: P3_U1.38 (PA15), P3_U8.5 (IN2)
P3/PEEL_M1: P3_J2.1, P3_TP6.1, P3_U8.2 (OUT1)
P3/PEEL_M2: P3_J2.2, P3_TP5.1, P3_U8.3 (OUT2)
P3/RESET: P3_J1.10 (~RESET), P3_J9.10 (~RESET), P3_R4.1, P3_U1.7 (NRST)
P3/RS-485+: P3_D2.2 (A2), P3_J5.4, P3_R15.2
P3/RS-485-: P3_D2.1 (A1), P3_J5.3, P3_R16.2
P3/SW1: P3_J4.1, P3_U1.19 (PB1)
P3/SW2: P3_J6.1, P3_U1.18 (PB0)
P3/SWCLK: P3_J1.4 (SWDCLK/TCK), P3_J9.4 (SWDCLK/TCK), P3_U1.37 (PA14)
P3/SWDIO: P3_J1.2 (SWDIO/TMS), P3_J9.2 (SWDIO/TMS), P3_U1.34 (PA13)
P3/~RE: P3_R18.1, P3_U1.32 (PA11), P3_U6.2 (~RE)
